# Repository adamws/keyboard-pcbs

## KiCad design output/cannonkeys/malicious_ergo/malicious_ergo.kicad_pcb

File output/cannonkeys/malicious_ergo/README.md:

## cannonkeys/malicious_ergo

[layout](malicious_ergo-kle.json) - [PCB](malicious_ergo.kicad_pcb)

{:loading="lazy"}

[Open in keyboard-layout-editor](http://www.keyboard-layout-editor.com/##@@_x:0.55&y:1.15&c=#777777;&=0,0&_x:15.95&c=#aaaaaa;&=0,16;&@_x:3.7&y:-0.95&c=#cccccc;&=0,3&_x:8.45;&=0,12;&@_x:1.7&y:-0.95;&=0,1&=0,2&_x:10.45;&=0,13&=0,14%0A%0A%0A0,0&_c=#aaaaaa;&=0,15%0A%0A%0A0,0;&@_x:0.35&y:-0.1;&=1,0&_x:16.4;&=1,16;&@_x:13&y:-0.95&c=#cccccc;&=1,12;&@_x:1.5&y:-0.95&c=#aaaaaa&w:1.5;&=1,1&_c=#cccccc;&=1,2&_x:10.0;&=1,13&=1,14&_c=#aaaaaa&w:1.5;&=1,15;&@_x:0.15&y:-0.1;&=2,0&_x:16.85;&=2,16;&@_x:13.4&y:-0.9&c=#cccccc;&=2,12&=2,13&_c=#777777&w:2.25;&=2,15&_x:-16.35&c=#aaaaaa&w:1.75;&=2,1&_c=#cccccc;&=2,2;&@_x:1.05&c=#aaaaaa&w:2.25;&=3,1&_c=#cccccc;&=3,2&_x:8.8;&=3,12&=3,13&_c=#aaaaaa&w:1.75;&=3,14&=3,15;&@_x:1.05&w:1.5;&=4,1&_x:11.2&w:1.5;&=4,13&_x:0.6;&=4,14&=4,15&=4,16;&@_r:12&x:5.05&y:-6.0&c=#cccccc;&=0,4&=0,5&=0,6&=0,7;&@_x:4.6;&=1,3&=1,4&=1,5&=1,6;&@_x:4.85;&=2,3&=2,4&=2,5&=2,6;&@_x:5.3;&=3,3&=3,4&=3,5&=3,6;&@_x:6.6&c=#777777&w:2;&=4,4&_c=#aaaaaa&w:1.25;&=4,6;&@_x:5.05&y:-0.95&w:1.5;&=4,3;&@_r:-12&x:8.45&y:-1.45&c=#cccccc;&=0,8&=0,9&=0,10&=0,11;&@_x:8.05;&=1,8&=1,9&=1,10&=1,11;&@_x:8.2;&=2,8&=2,9&=2,10&=2,11;&@_x:7.75;&=3,8&=3,9&=3,10&=3,11;&@_x:7.75&c=#777777&w:2.75;&=4,9;&@_x:10.55&y:-0.95&c=#aaaaaa&w:1.5;&=4,11;&@_r:0&x:15.15&y:-8.75&w:2;&=0,15%0A%0A%0A0,1)

{:loading="lazy"}

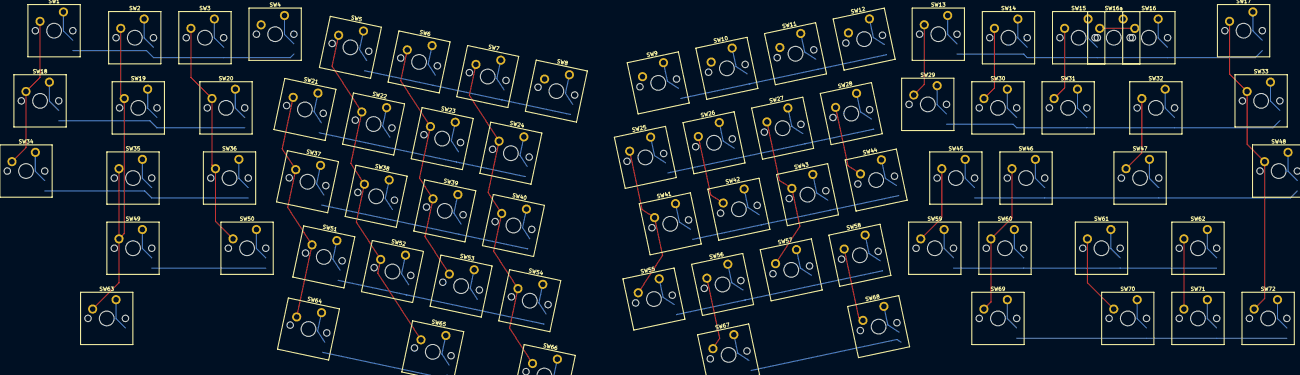
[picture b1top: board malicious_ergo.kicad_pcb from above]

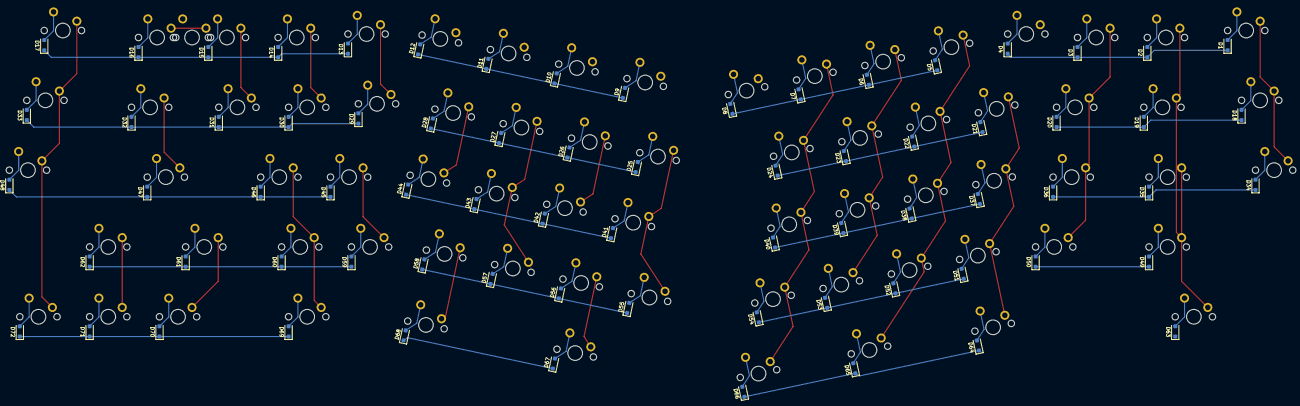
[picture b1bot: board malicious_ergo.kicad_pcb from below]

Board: 2 copper layers, 145 parts (72 on the bottom side), 93 nets.

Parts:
D1, D2, D3, D4, D5, D6, D7, D8, D9, D10, D11, D12, D13, D14, D15, D16, D17, D18, D19, D20, D21, D22, D23, D24, D25, D26, D27, D28, D29, D30, D31, D32, D33, D34, D35, D36, D37, D38, D39, D40, D41, D42, D43, D44, D45, D46, D47, D48, D49, D50, D51, D52, D53, D54, D55, D56, D57, D58, D59, D60, D61, D62, D63, D64, D65, D66, D67, D68, D69, D70, D71, D72: D_SOD-123F
SW1, SW2, SW3, SW4, SW5, SW6, SW7, SW8, SW9, SW10, SW11, SW12, SW13, SW14, SW15, SW16, SW16a, SW17, SW18, SW19, SW20, SW21, SW22, SW23, SW24, SW25, SW26, SW27, SW28, SW29, SW30, SW31, SW32, SW33, SW34, SW35, SW36, SW37, SW38, SW39, SW40, SW41, SW42, SW43, SW44, SW45, SW46, SW47, SW48, SW49, SW50, SW51, SW52, SW53, SW54, SW55, SW56, SW57, SW58, SW59, SW60, SW61, SW62, SW63, SW64, SW65, SW66, SW67, SW68, SW69, SW70, SW71, SW72: SW_Cherry_MX_PCB_1.00u

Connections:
COL0: SW1.1, SW18.1, SW34.1
COL1: SW2.1, SW19.1, SW35.1, SW49.1, SW63.1
COL2: SW3.1, SW20.1, SW36.1, SW50.1
COL3: SW4.1, SW21.1, SW37.1, SW51.1, SW64.1
COL4: SW5.1, SW22.1, SW38.1, SW52.1, SW65.1
COL5: SW6.1, SW23.1, SW39.1, SW53.1
COL6: SW7.1, SW24.1, SW40.1, SW54.1, SW66.1
COL8: SW9.1, SW25.1, SW41.1, SW55.1
COL9: SW10.1, SW26.1, SW42.1, SW56.1, SW67.1
COL10: SW11.1, SW27.1, SW43.1, SW57.1
COL11: SW12.1, SW28.1, SW44.1, SW58.1, SW68.1
COL12: SW13.1, SW29.1, SW45.1, SW59.1
COL13: SW14.1, SW30.1, SW46.1, SW60.1, SW69.1
COL14: SW15.1, SW31.1, SW61.1, SW70.1
COL15: SW16.1, SW16a.1, SW32.1, SW47.1, SW62.1, SW71.1
COL16: SW17.1, SW33.1, SW48.1, SW72.1
unnamed: D1.2, SW1.2
unnamed: D2.2, SW2.2
unnamed: D3.2, SW3.2
unnamed: D4.2, SW4.2
unnamed: D5.2, SW5.2
unnamed: D6.2, SW6.2
unnamed: D7.2, SW7.2
unnamed: D8.2, SW8.2
unnamed: D9.2, SW9.2
unnamed: D10.2, SW10.2
unnamed: D11.2, SW11.2
unnamed: D12.2, SW12.2
unnamed: D13.2, SW13.2
unnamed: D14.2, SW14.2
unnamed: D15.2, SW15.2
unnamed: D16.2, SW16.2, SW16a.2
unnamed: D17.2, SW17.2
unnamed: D18.2, SW18.2
unnamed: D19.2, SW19.2
unnamed: D20.2, SW20.2
unnamed: D21.2, SW21.2
unnamed: D22.2, SW22.2
unnamed: D23.2, SW23.2
unnamed: D24.2, SW24.2
unnamed: D25.2, SW25.2
unnamed: D26.2, SW26.2
unnamed: D27.2, SW27.2
unnamed: D28.2, SW28.2
unnamed: D29.2, SW29.2
unnamed: D30.2, SW30.2
unnamed: D31.2, SW31.2
unnamed: D32.2, SW32.2
unnamed: D33.2, SW33.2
unnamed: D34.2, SW34.2
unnamed: D35.2, SW35.2
unnamed: D36.2, SW36.2
unnamed: D37.2, SW37.2
unnamed: D38.2, SW38.2
unnamed: D39.2, SW39.2
unnamed: D40.2, SW40.2
unnamed: D41.2, SW41.2
unnamed: D42.2, SW42.2
unnamed: D43.2, SW43.2
unnamed: D44.2, SW44.2
unnamed: D45.2, SW45.2
unnamed: D46.2, SW46.2
unnamed: D47.2, SW47.2
unnamed: D48.2, SW48.2
unnamed: D49.2, SW49.2
unnamed: D50.2, SW50.2
unnamed: D51.2, SW51.2
unnamed: D52.2, SW52.2
unnamed: D53.2, SW53.2
unnamed: D54.2, SW54.2
unnamed: D55.2, SW55.2
unnamed: D56.2, SW56.2
unnamed: D57.2, SW57.2
unnamed: D58.2, SW58.2
unnamed: D59.2, SW59.2
unnamed: D60.2, SW60.2
unnamed: D61.2, SW61.2
unnamed: D62.2, SW62.2
unnamed: D63.2, SW63.2
unnamed: D64.2, SW64.2
unnamed: D65.2, SW65.2
unnamed: D66.2, SW66.2
unnamed: D67.2, SW67.2
unnamed: D68.2, SW68.2
unnamed: D69.2, SW69.2
unnamed: D70.2, SW70.2
unnamed: D71.2, SW71.2
unnamed: D72.2, SW72.2
ROW0: D1.1, D2.1, D3.1, D4.1, D5.1, D6.1, D7.1, D8.1, D9.1, D10.1, D11.1, D12.1, D13.1, D14.1, D15.1, D16.1, D17.1
ROW1: D18.1, D19.1, D20.1, D21.1, D22.1, D23.1, D24.1, D25.1, D26.1, D27.1, D28.1, D29.1, D30.1, D31.1, D32.1, D33.1
ROW2: D34.1, D35.1, D36.1, D37.1, D38.1, D39.1, D40.1, D41.1, D42.1, D43.1, D44.1, D45.1, D46.1, D47.1, D48.1
ROW3: D49.1, D50.1, D51.1, D52.1, D53.1, D54.1, D55.1, D56.1, D57.1, D58.1, D59.1, D60.1, D61.1, D62.1
ROW4: D63.1, D64.1, D65.1, D66.1, D67.1, D68.1, D69.1, D70.1, D71.1, D72.1
